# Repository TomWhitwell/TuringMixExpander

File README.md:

## Turing Vactrol Mix Expander   

](https://github.com/TomWhitwell/TuringMixExpander/raw/master/Collateral/vme_vid1.png)  

- A 4 in, 2 out  vactrol matrix mixer controlled by the Turing Machine  
- Connects to the Gates output, can be daisychained with Voltages  
- Creates rhythmic patterns or shifting drones from any audio source 
- Great for feedback loops  
- DC coupled, so you can also rhythmically cut up DC sources; LFOs etc. 
- Inspired by Grant Richter's Cadavre Exquis voltage controlled mixer.  
- NB: Fully expanded Turing (Pulses, Voltages, Vactrol) draws up to 190mA of current, so you may need to upgrade (or short circuit) the polyfuses in your backpack. 

### Resources  

[Documentation](https://github.com/TomWhitwell/TuringMixExpander/wiki)   
[Patch Ideas](https://github.com/TomWhitwell/TuringMixExpander/wiki/Patch-Recipes)  
[Manual](https://github.com/TomWhitwell/TuringMixExpander/wiki/How-to-use-the-module)  
[Issue Log](https://github.com/TomWhitwell/TuringMixExpander/issues)   
[Schematic](https://github.com/TomWhitwell/TuringMixExpander/wiki/Schematics)  

There is no PCB Panel layout, but there is a prototype lasercut panel in the hardware folder.  

### Demos: 
[Video 1: General demo](http://youtu.be/Ccwjb2riCqE)  
[Video 2](http://youtu.be/xf4IhIy3am4)  
[Video 3](http://youtu.be/hwUs_kbf3PM)  
[Vactrol Mix Expander 1](https://soundcloud.com/musicthing/random-looping-vactrol-mixer)  
[Vactrol Mix Expander 2](https://soundcloud.com/musicthing/exquisite-corpse-2)  
[20 Minutes of Madness](https://soundcloud.com/musicthing/radio-music-20-minutes-of-madness)  

This module design is Creative Commons Licensed by Tom Whitwell: CC-BY-SA

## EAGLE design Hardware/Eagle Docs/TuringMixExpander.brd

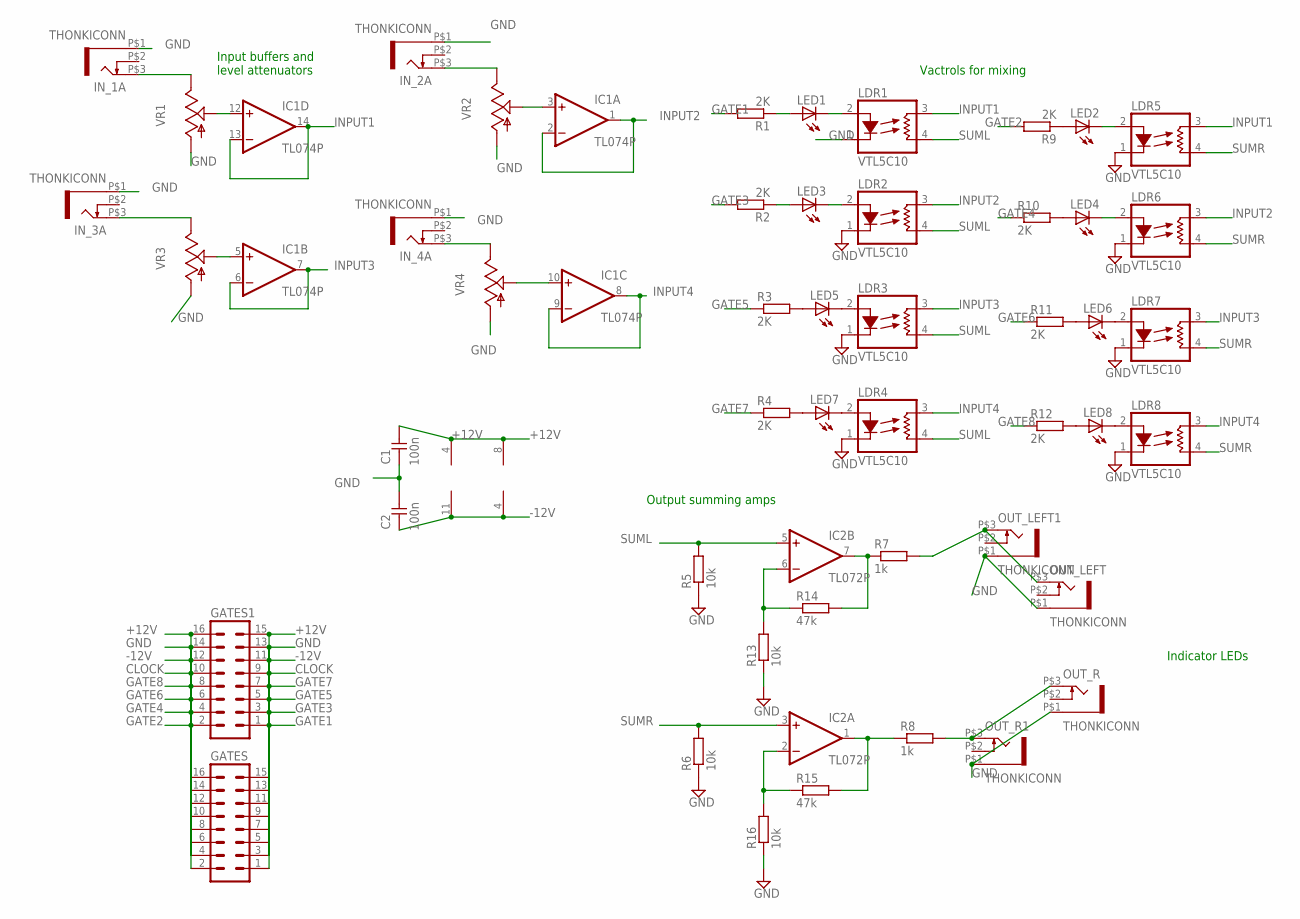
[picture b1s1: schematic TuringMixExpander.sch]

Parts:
C1, C2: 100n; C050-024X044
GATES, GATES1: MA08-2
IC1: TL074P; DIL14
IC2: TL072P; DIL08
IN_1A, IN_2A, IN_3A, IN_4A: THONKICONN
LDR1, LDR2, LDR3, LDR4, LDR5, LDR6, LDR7, LDR8: VTL5C10; VTL5C
LED1, LED2, LED3, LED4, LED5, LED6, LED7, LED8: LED3MM
OUT_LEFT, OUT_LEFT1: THONKICONN
OUT_R, OUT_R1: THONKICONN
R1, R2, R3, R4, R9, R10, R11, R12: 2K; 0207/7
R5, R6, R13, R16: 10k; 0207/7
R7, R8: 1k; 0207/7
R14, R15: 47k; 0207/7
VR1, VR2, VR3, VR4: ALPHA-9MMF2A; EVUF

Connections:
+12V: C1.1, GATES.15, GATES.16, GATES1.15, GATES1.16, IC1.4 (V+), IC2.8 (V+)
-12V: C2.2, GATES.11, GATES.12, GATES1.11, GATES1.12, IC1.11 (V-), IC2.4 (V-)
CLOCK: GATES.9, GATES.10, GATES1.9, GATES1.10
GATE1: GATES.1, GATES1.1, R1.2
GATE2: GATES.2, GATES1.2, R9.2
GATE3: GATES.3, GATES1.3, R2.2
GATE4: GATES.4, GATES1.4, R10.1
GATE5: GATES.5, GATES1.5, R3.1
GATE6: GATES.6, GATES1.6, R11.1
GATE7: GATES.7, GATES1.7, R4.1
GATE8: GATES.8, GATES1.8, R12.1
GND: C1.2, C2.1, GATES.13, GATES.14, GATES1.13, GATES1.14, IN_1A.P$1 (5), IN_2A.P$1 (5), IN_3A.P$1 (5), IN_4A.P$1 (5), LDR1.1 (LED-), LDR2.1 (LED-), LDR3.1 (LED-), LDR4.1 (LED-), LDR5.1 (LED-), LDR6.1 (LED-), LDR7.1 (LED-), LDR8.1 (LED-), OUT_LEFT.P$1 (5), OUT_LEFT1.P$1 (5), OUT_R.P$1 (5), OUT_R1.P$1 (5), R5.1, R6.1, R13.1, R16.1, VR1.1 (A), VR2.1 (A), VR3.1 (A), VR4.1 (A)
INPUT1: IC1.13 (-IN), IC1.14 (OUT), LDR1.3 (RES1), LDR5.3 (RES1)
INPUT2: IC1.1 (OUT), IC1.2 (-IN), LDR2.3 (RES1), LDR6.3 (RES1)
INPUT3: IC1.6 (-IN), IC1.7 (OUT), LDR3.3 (RES1), LDR7.3 (RES1)
INPUT4: IC1.8 (OUT), IC1.9 (-IN), LDR4.3 (RES1), LDR8.3 (RES1)
unnamed: IN_1A.P$3 (3), VR1.3 (E)
unnamed: IC1.12 (+IN), VR1.2 (S)
unnamed: IN_2A.P$3 (3), VR2.3 (E)
unnamed: IC1.3 (+IN), VR2.2 (S)
unnamed: IC2.7 (OUT), R7.1, R14.2
unnamed: OUT_R.P$3 (3), OUT_R1.P$3 (3), R8.2
unnamed: IC2.6 (-IN), R13.2, R14.1
unnamed: IC2.2 (-IN), R15.1, R16.2
unnamed: IC1.5 (+IN), VR3.2 (S)
unnamed: IN_3A.P$3 (3), VR3.3 (E)
unnamed: IN_4A.P$3 (3), VR4.3 (E)
unnamed: LDR1.2 (LED+), LED1.K (C)
unnamed: LDR2.2 (LED+), LED3.K (C)
unnamed: LDR3.2 (LED+), LED5.K (C)
unnamed: LDR4.2 (LED+), LED7.K (C)
unnamed: LDR5.2 (LED+), LED2.K (C)
unnamed: LDR6.2 (LED+), LED4.K (C)
unnamed: LDR7.2 (LED+), LED6.K (C)
unnamed: LDR8.2 (LED+), LED8.K (C)
unnamed: OUT_LEFT.P$3 (3), OUT_LEFT1.P$3 (3), R7.2
unnamed: IC1.10 (+IN), VR4.2 (S)
unnamed: IC2.1 (OUT), R8.1, R15.2
unnamed: LED1.A, R1.1
unnamed: LED3.A, R2.1
unnamed: LED5.A, R3.2
unnamed: LED7.A, R4.2
unnamed: LED2.A, R9.1
unnamed: LED4.A, R10.2
unnamed: LED6.A, R11.2
unnamed: LED8.A, R12.2
SUML: IC2.5 (+IN), LDR1.4 (RES2), LDR2.4 (RES2), LDR3.4 (RES2), LDR4.4 (RES2), R5.2
SUMR: IC2.3 (+IN), LDR5.4 (RES2), LDR6.4 (RES2), LDR7.4 (RES2), LDR8.4 (RES2), R6.2

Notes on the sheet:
Input buffers and level attenuators
Vactrols for mixing
Indicator LEDs
Output summing amps

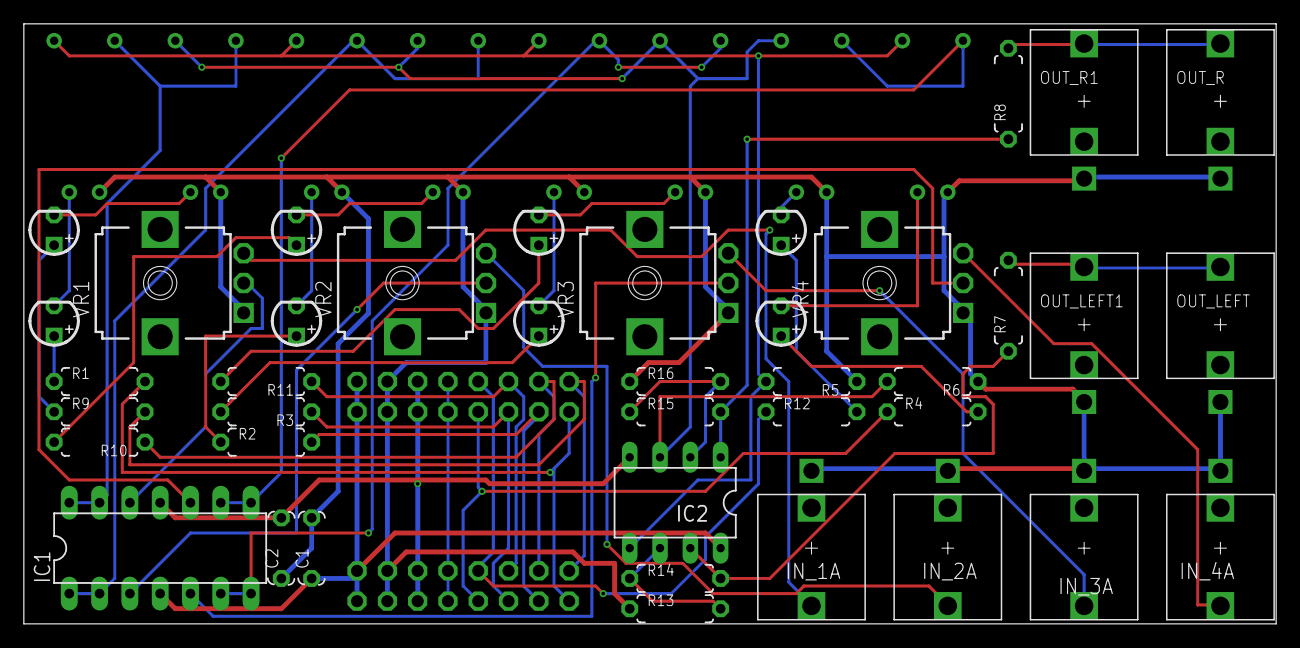
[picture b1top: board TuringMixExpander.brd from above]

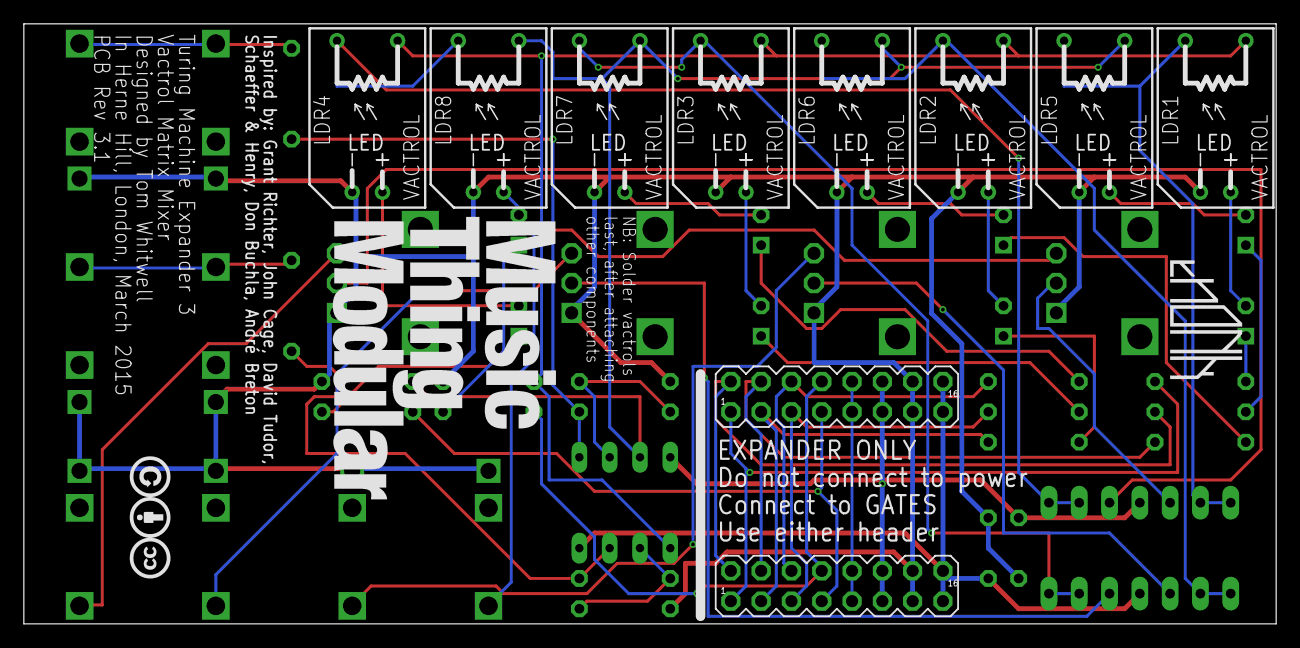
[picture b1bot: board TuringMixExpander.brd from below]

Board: 4 copper layers, 105.0 x 50.3 mm, 53 parts (13 on the bottom side), 48 nets.

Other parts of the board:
U$1: MTM_2CM
U$2: CC_1CM_SCREENPRINT
U$3: THONK_1CM_SCREENPRINT

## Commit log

2014-11-15 Upload working files
2014-11-15 Readme
2015-01-17 Images for Exquisite Corpse
2015-01-21 Add schematic
2015-01-21 add schematic image
2015-01-21 Upload panel artwork
2015-01-22 add panel image
2015-01-22 Upload video image
2015-02-05 New pcb layout
    Added passthrough header
    Removed resistor networks
    Simplified led/resistor structure (one per channel, not two)
    New panel layout
2015-02-12 New resistor grid
2015-02-13 PCB work
2015-03-13 Gerbers manufactured OSHPark
2015-03-18 Rev 3.1 Gerbers for OSH Park
2015-06-13 Prototype Lasercut Panel Artwork
2015-06-13 image
2015-11-05 Image upload, some schematic tidying
2022-10-05 Corrected markup for headings
